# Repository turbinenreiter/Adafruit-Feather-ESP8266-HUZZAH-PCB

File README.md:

# Adafruit-Feather-ESP8266-HUZZAH-PCB-lowcost

This is an _untested_ adaption of the original Feather HUZZAH that removes just about everything to provide an ultra-low cost DIY version to permanently leave in projects.

PCB files for the Adafruit Feather ESP8266 HUZZAH

Format is EagleCAD schematic and board layout

For more details, check out the product page at

  * https://www.adafruit.com/product/2821

Adafruit invests time and resources providing this open source design, 
please support Adafruit and open-source hardware by purchasing 
products from Adafruit!

Designed by Adafruit Industries.  
Creative Commons Attribution, Share-Alike license, check license.txt for more information
All text above must be included in any redistribution

Adapted by Sebastian Plamauer

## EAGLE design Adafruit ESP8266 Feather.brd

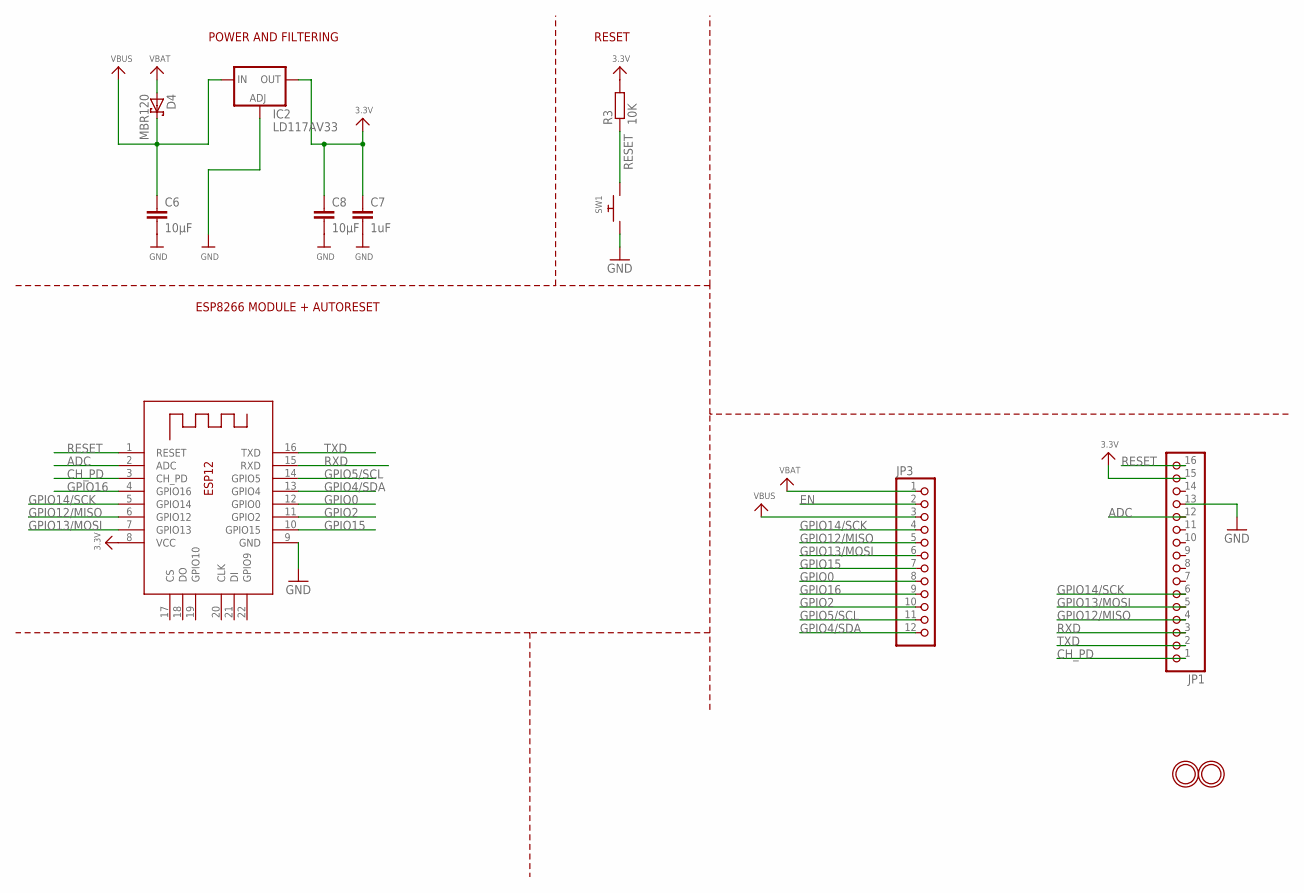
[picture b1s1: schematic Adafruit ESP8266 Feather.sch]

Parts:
C6, C8: 10µF; C025-024X044
C7: 1uF; C025-024X044
D4: MBR120; DO41-7
IC2: LD117AV33; TO220L1
JP1: HEADER-1X16ROUND; 1X16_ROUND
JP3: HEADER-1X12; 1X12_ROUND
R3: 10K; 0204/5
SW1: SWITCH_PUSHBUTTONEVQ-PE; TACT_PANA-EVQ
U$31, U$32: MOUNTINGHOLE2.5; MOUNTINGHOLE_2.5_PLATED
X2: ESP-12; ESP-12E

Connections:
3.3V: C7.1, C8.1, IC2.2 (OUT), JP1.15, R3.2, X2.8 (VCC)
ADC: JP1.12, X2.2 (ADC)
CH_PD: JP1.1, X2.3 (CH_PD)
EN: JP3.2
GND: C6.2, C7.2, C8.2, IC2.1 (ADJ), JP1.13, SW1.P$2, X2.9 (GND)
GPIO0: JP3.8, X2.12 (GPIO0)
GPIO2: JP3.10, X2.11 (GPIO2)
GPIO4/SDA: JP3.12, X2.13 (GPIO4)
GPIO5/SCL: JP3.11, X2.14 (GPIO5)
GPIO12/MISO: JP1.4, JP3.5, X2.6 (GPIO12)
GPIO13/MOSI: JP1.5, JP3.6, X2.7 (GPIO13)
GPIO14/SCK: JP1.6, JP3.4, X2.5 (GPIO14)
GPIO15: JP3.7, X2.10 (GPIO15)
GPIO16: JP3.9, X2.4 (GPIO16)
RESET: JP1.16, R3.1, SW1.P$1, X2.1 (RESET)
RXD: JP1.3, X2.15 (RXD)
TXD: JP1.2, X2.16 (TXD)
VBAT: D4.A, JP3.1
VBUS: C6.1, D4.C, IC2.3 (IN), JP3.3

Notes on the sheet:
POWER AND FILTERING
RESET
ESP8266 MODULE + AUTORESET

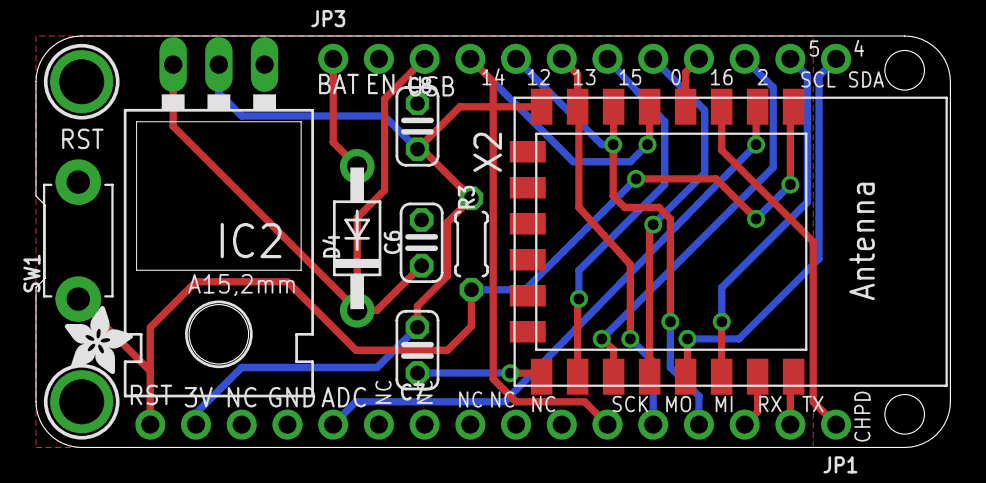
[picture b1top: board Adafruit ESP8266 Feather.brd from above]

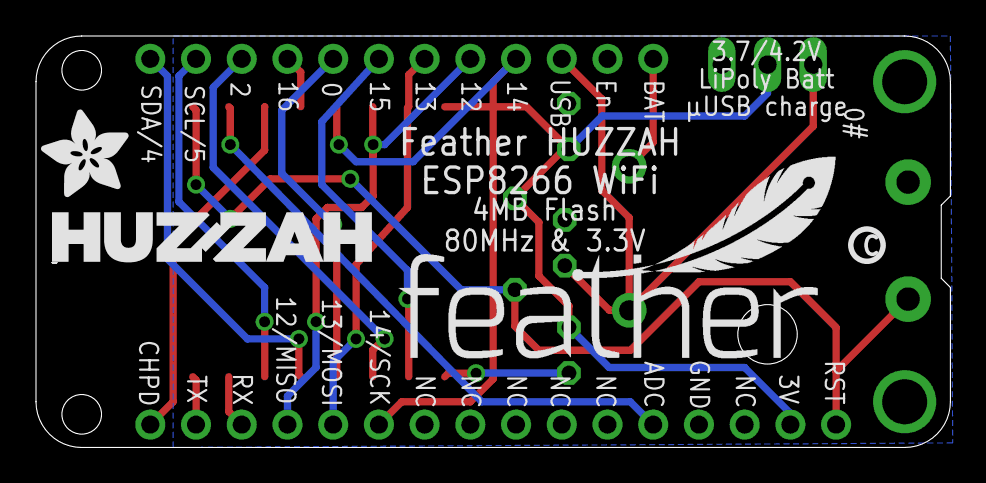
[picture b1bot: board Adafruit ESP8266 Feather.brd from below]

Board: 2 copper layers, 50.8 x 22.9 mm, 17 parts (4 on the bottom side), 18 nets.

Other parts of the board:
U$7: ADAFRUIT_5MM
U$9: FEATHERLOGO
U$13: PCBFEAT-REV-040
U$15: ADAFRUIT_3.5MM
U$23: HUZZAHLOGO

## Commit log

2016-03-07 init
2016-09-12 added low cost version
2016-09-12 through hole parts

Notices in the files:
parts and their libraries:
microbuilder: This work is placed in the public domain, and may be freely used for commercial and non-commercial work with the following conditions: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
